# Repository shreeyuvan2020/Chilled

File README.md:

Inspiration

I created this macropad so that as the name suggests, chill. I wanted to be able to do things quick and easily by using shortcuts through the macropad.

Challenges

This was my first time using autodesk fusion, and my first time ever designing a PCB! Even though at times I struggled with extruding sketches and routing the PCB, I went through the tutorial and got a LOT of help from people on the slack. 

Specifications

BOM:

- 4x Cherry MX Switches
- 2x SK6812 MINI Leds
- 1x XIAO RP2040
- 4x Blank DSA Keycaps
- 4x M3x16 Bolt
- 4x M3 Heatset Inserts
- 1x EC11 Rotary Encoder

Others:

- KMK Firmware
- Final.stl
- FrontCase v3.stl

PCB            |  Case         |   Schematic
:-------------------------:|:-------------------------:|:-------------------------:|
    |    |

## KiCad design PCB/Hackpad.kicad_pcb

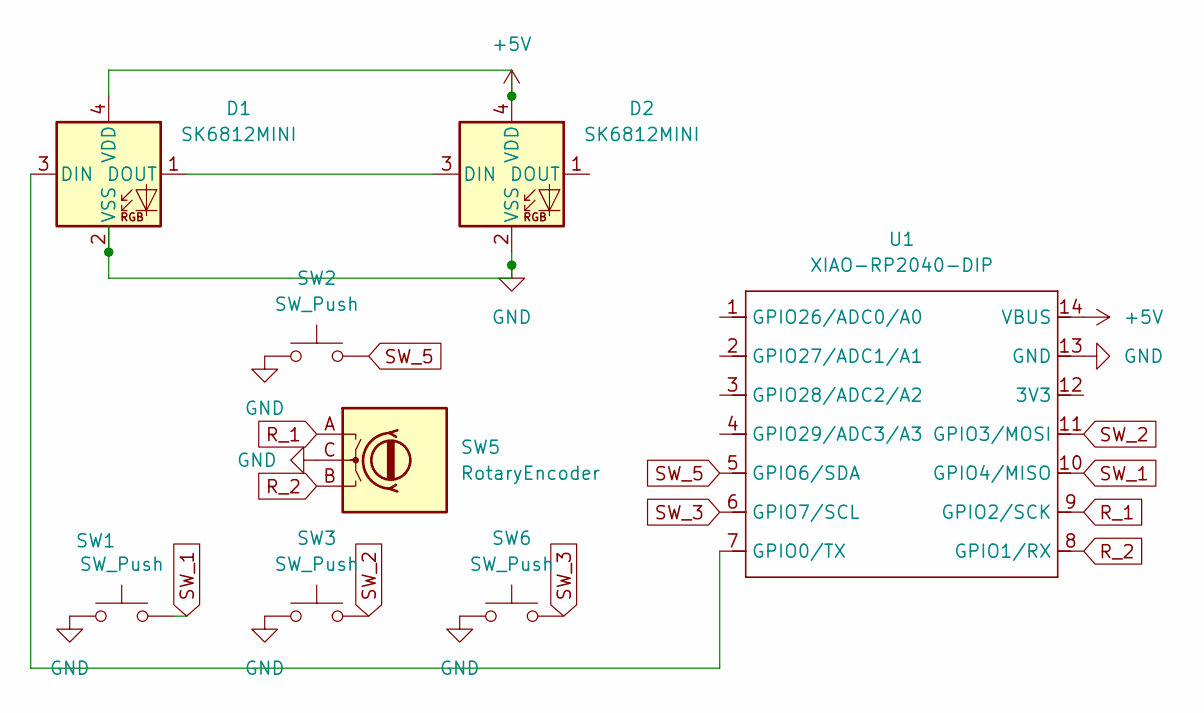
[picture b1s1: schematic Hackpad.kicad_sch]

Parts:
D1, D2: SK6812MINI; LED_SK6812MINI_PLCC4_3.5x3.5mm_P1.75mm
SW1, SW2, SW3: SW_Push; SW_Cherry_MX_1.00u_PCB
SW5: RotaryEncoder; RotaryEncoder_Alps_EC11E_Vertical_H20mm
SW6: SW_Push; SW_Cherry_MX_1.00u_Plate
U1: XIAO-RP2040-DIP

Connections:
+5V: D1.4 (VDD), D2.4 (VDD), U1.14 (VBUS)
GND: D1.2 (VSS), D2.2 (VSS), SW1.1, SW2.1, SW3.1, SW5.C, SW6.1, U1.13 (GND)
unnamed: D1.3 (DIN), U1.7 (GPIO0/TX)
unnamed: D1.1 (DOUT), D2.3 (DIN)
R_1: SW5.A, U1.9 (GPIO2/SCK)
R_2: SW5.B, U1.8 (GPIO1/RX)
SW_1: SW1.2, U1.10 (GPIO4/MISO)
SW_2: SW3.2, U1.11 (GPIO3/MOSI)
SW_3: SW6.2, U1.6 (GPIO7/SCL)
SW_5: SW2.2, U1.5 (GPIO6/SDA)

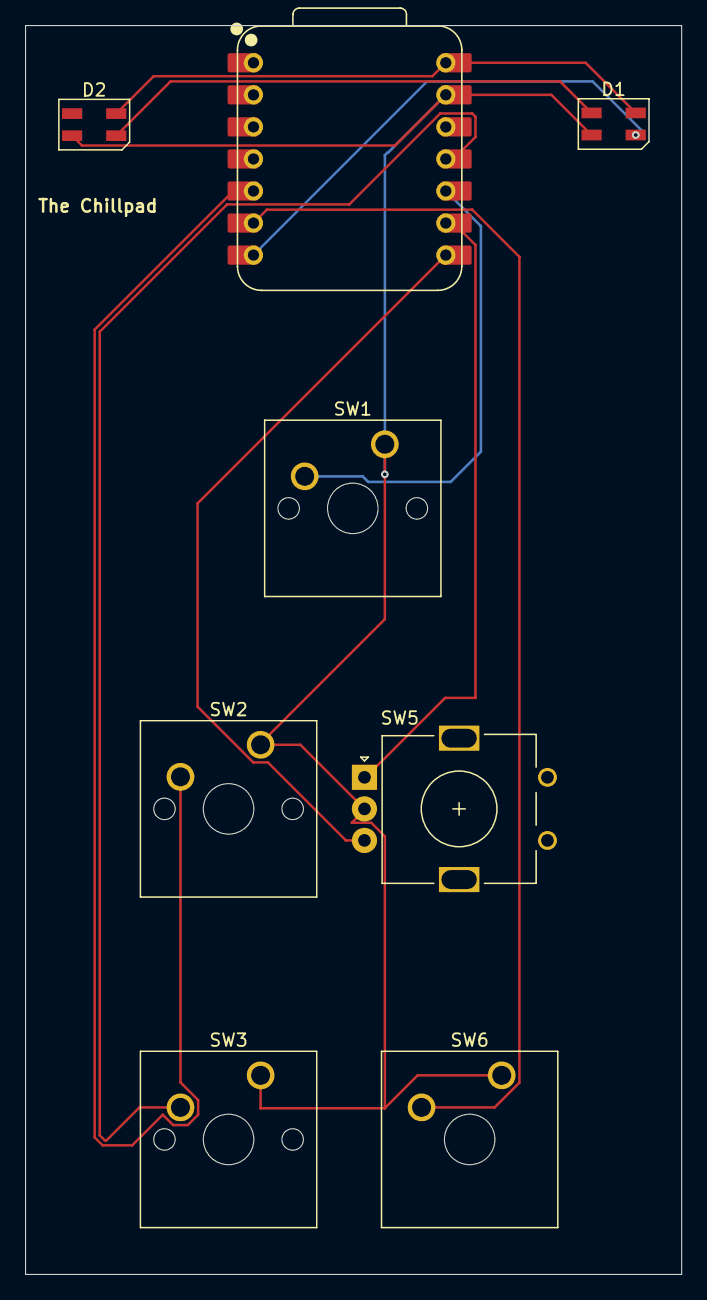
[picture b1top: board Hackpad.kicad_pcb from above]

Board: 2 copper layers, 52.0 x 99.0 mm, 8 parts (0 on the bottom side), 10 nets.

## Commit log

2025-05-31 First one!
2025-06-01 Gerbers!
2025-06-01 Gerbers
2025-06-08 Add BOM and images and other cool stuff
2025-06-08 Formatting changes
2025-06-09 Create dsf
2025-06-09 All my production stuff
2025-06-09 Added PCB files
2025-06-14 Add good files
